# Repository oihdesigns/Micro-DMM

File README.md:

# Update Late August '25: 
I've recently started a new job. It's great, but has longer hours than my previous job. This will negatively affect the amount of time I put into this project...

# Micro-DMM

This is the PCB design and code for a 4.5 digit DMM/ instrumentation module. It is designed and written primairly for Arduino-style development boards.

I've developed this DMM in my work testing and troubleshooting electronics to make my life easier. 

I've had Deep-Wiki index my documentation. It did a mostly okay job. You can read its summary here:

## The main features are:

- The most recent designs have **open-lead detection in voltmeter mode**. I believe this makes it the first voltmeter in exisitance that can automatically, safely, and positively tell the difference between "there is low impedance between these points" vs "current does not and can not flow between these two points." Please see the white paper for details. 
- Using keyboard emulation to directly type values into a computer for me. (Extremely useful when troubleshooting a populated PCB - you can quickly ohm out both the problem board and a good one directly into Excel to look for different impedances between given contacts.)
- Very sensitive low-resistance readings (accurate to better than 0.01 Ohms with proper lead zeroing).
- LED blinks when I'm reading logic level voltage or higher.
- Simultaneous current and voltage measurement abilities (requires a Hall sensor-based ammeter module). 
- Data logging for current and voltage, with customizable triggers to autolog both.

## Raspberry Pi user interface

The repository now includes a Raspberry Pi-friendly interface that mirrors the firmware display and logging features. The UI is written in Python using Tkinter so it ships with Raspberry Pi OS and can run directly on the framebuffer or under X11. To start the dashboard with the built-in demo generator run:

```
python3 -m raspi_port.app
```

In deployment the measurement host should feed real readings to the `MicroDmmApp` class instead of the demo thread. The window presents the same information rendered by `updateDisplay()`—live voltage or resistance with min/max tracking, current when enabled, the active mode, timestamps, delta/null information, and log counters. Interaction hotkeys replace the touch panel:

| Function | Touch color | Hotkey | Description |
| --- | --- | --- | --- |
| Mode cycle | Red | `M` | Advances through the measurement modes. |
| Manual log | Green | `L` | Appends the most recent sample buffer to `~/micro_dmm_logs/data.csv`. |
| Auto log export | – | `A` | Writes the auto-log buffer to `~/micro_dmm_logs/data_autologged.csv`. |
| Min/Max reset | Blue | `Z` | Clears the stored extrema, just like tapping “Min/Max”. |
| Type/Δ | Yellow | `T` | In *Type* mode it writes the displayed value to `typed_entries.txt`; otherwise it arms the delta/null workflow. |

On a Raspberry Pi you can optionally map these controls to hardware buttons by defining a `MICRO_DMM_GPIO` environment variable before launching the program. The value is a comma-separated list such as `mode=5,manual_log=6,auto_log=13,minmax=19,type=26`. Each entry binds a GPIO pin (using `gpiozero.Button`) to the corresponding action.

All log exports stay on the Pi’s filesystem under `~/micro_dmm_logs/`. The CSV layouts match the firmware’s `logCurrentData()` and `autologArraysToCSV()` routines so downstream tooling continues to work. The `typed_entries.txt` file replaces the USB keyboard emulator and captures the same formatted text that would have been “typed” into a host PC, while also echoing it to stdout for quick clipboard-style use.

I have a long and detailed write-up of the circuitry design on my personal website: https://www.oihdesigns.com/arduino-multimeter-project

There are a couple videos here:
https://youtu.be/rzj-ar2Qv_A
and here:
https://youtu.be/hZ4eH-7RNsU

Here are more photos:

## Design Prioities and Compromises:
This meter is designed to complement and support the more expensive equimpent generally found in a lab, rather than replace it. With that in mide, I've made the following design decisions on my priorites:

### Minimal Protections
- The voltmeter circuitry is not designed to measure amplitudes higher than is dangerous to humans. By not designing a tool that is supposed to keep people safe I can dramatically simplify and shrink the design. (The said, I've nailed the voltmeter circuit with a 1000V megaohmmeter. No problem.)
- Likewise, the resistance circuit can be damaged if you accidentally measure too much /unregulated voltage. This is a tradeoff for a very fast and accurate autoranging ohmmeter circuit that can accurately read from less than 0.01 to more than 5,000,000 Ohms. 

### Streamlined Functions
- There is no built in ammeter, inductance, or capacitance function. Ammeter function is easily added as needed with either an off-the-shelf module, or a low value resistor across the voltmeter. There isn't an easy way to add indutance or capacitance. I don't use any of these often enough for them to be worth taking up the PCB space.  

## Current Support:
As of writing I have functional versions (I confirmed the core functions work) that support the:
- Arduino Uno R4
- Arduino Giga (with or without the display shield)
- Arduino ESP32 Nano (via jumpers)
- Seeed Studio XIAO RA4M1 (same processer as the Uno R4)
- I have partial function on a direct computer (Windows 11) interface with a FT232H breakout board (AdaFruit makes a nice one). I can see the data lines and it looks like most of the logic works, more or less. It's a proof of concept port and a test for "can I tell the AI to take an Arduino sketch and port it to Python" (the answer is far more yes than it use to be).
  -  That said, it's very slow (reading in at 2-3sps). I'm not sure how to optimize this, and speeding it up is not an immediate priority. 

# Future Plans:

## Major Function Things to Address:
- Writing to MicroSD cards over the AUX SPI Bux on the RA4M1 XIAO boards. I set this up and tested it, but it didn't work and needs to be troubleshot.
- Getting the code to run on the XIAO RP2350 board. It compiles but does not run. 

## Potential Refinements To-Do List:
- Revise the PCB design to shrink the physical size (the current design was made with hand-soldering in mind). This would involve:
  - Smaller footprint components for things like the pullup resistors.
  - Dedicated multiple transistor packages for the switching functions rather than the discreet components.
  - There are probably other ways to shrink the design.
  - There is some potential performance improvement room to the analog circuit if I take advantage of the ADS1115's max input voltage of ~6.144vdc instead of 5vdc.
- There is always room for cleanup in the code to make it more elegant. 

## Ideas for Expanding on the Current Function / :
- Make a version that uses an ADS1256 instead of the ADS1115 to support measurements speeds up to 30,000 samples/second and resolutions of up to 24bits. (I have had proof-of-concept success with this using a Raspberry PI ADS1256 hat.)
- Make a version that runs off a Raspberry Pi.
- Implement WiFi/Bluetooth features on the boards that support it.
- Implement DAC output as a simple function generator for the boards that support it.
- Add a jumper on the PCB and write the code to allow four-wire resistance readings.

If you're interested in helping develop this please feel free to reach out. 

# FAQ:
- Q: What is the logic voltage?
  - A:  The current PCB works for either 3.3 or 5vdc. 

- Q: Is there voltage isolation on the USB?
  - A: There is enough isolation (500K Ohms) that you will not hurt anything by measuring voltage (in either polarity) on something connected to the wall while the meter is also connected to the wall, but not enough to prevent ground loops from interfering with measurements. See the longer, full write up on my website, and then buy the Adafruit USB voltage isolation board.

- Q: The Adafruit isolation board says "100mA." What does the meter draw?
  - A: With the XIAO RA4M1, 50-60mA typical when measuring voltage. Closer to 100mA when measuring resistance. The resistance circuit goes into low-power mode several seconds after being open (except in a no-sleep mode).

- Q: Does it work on an Arduino Uno R3?
  - A: As a basic meter, yes, but there's no keyboard emulation.    

- Q: Can I buy one?
  - A: Eventually, yes, probably? I do not have a current timeline for bringing these to market. If you want one please reach out to me. If you want to hand-solder it yourself I can sell you a single PCB and maybe some of the components with higher individual costs.

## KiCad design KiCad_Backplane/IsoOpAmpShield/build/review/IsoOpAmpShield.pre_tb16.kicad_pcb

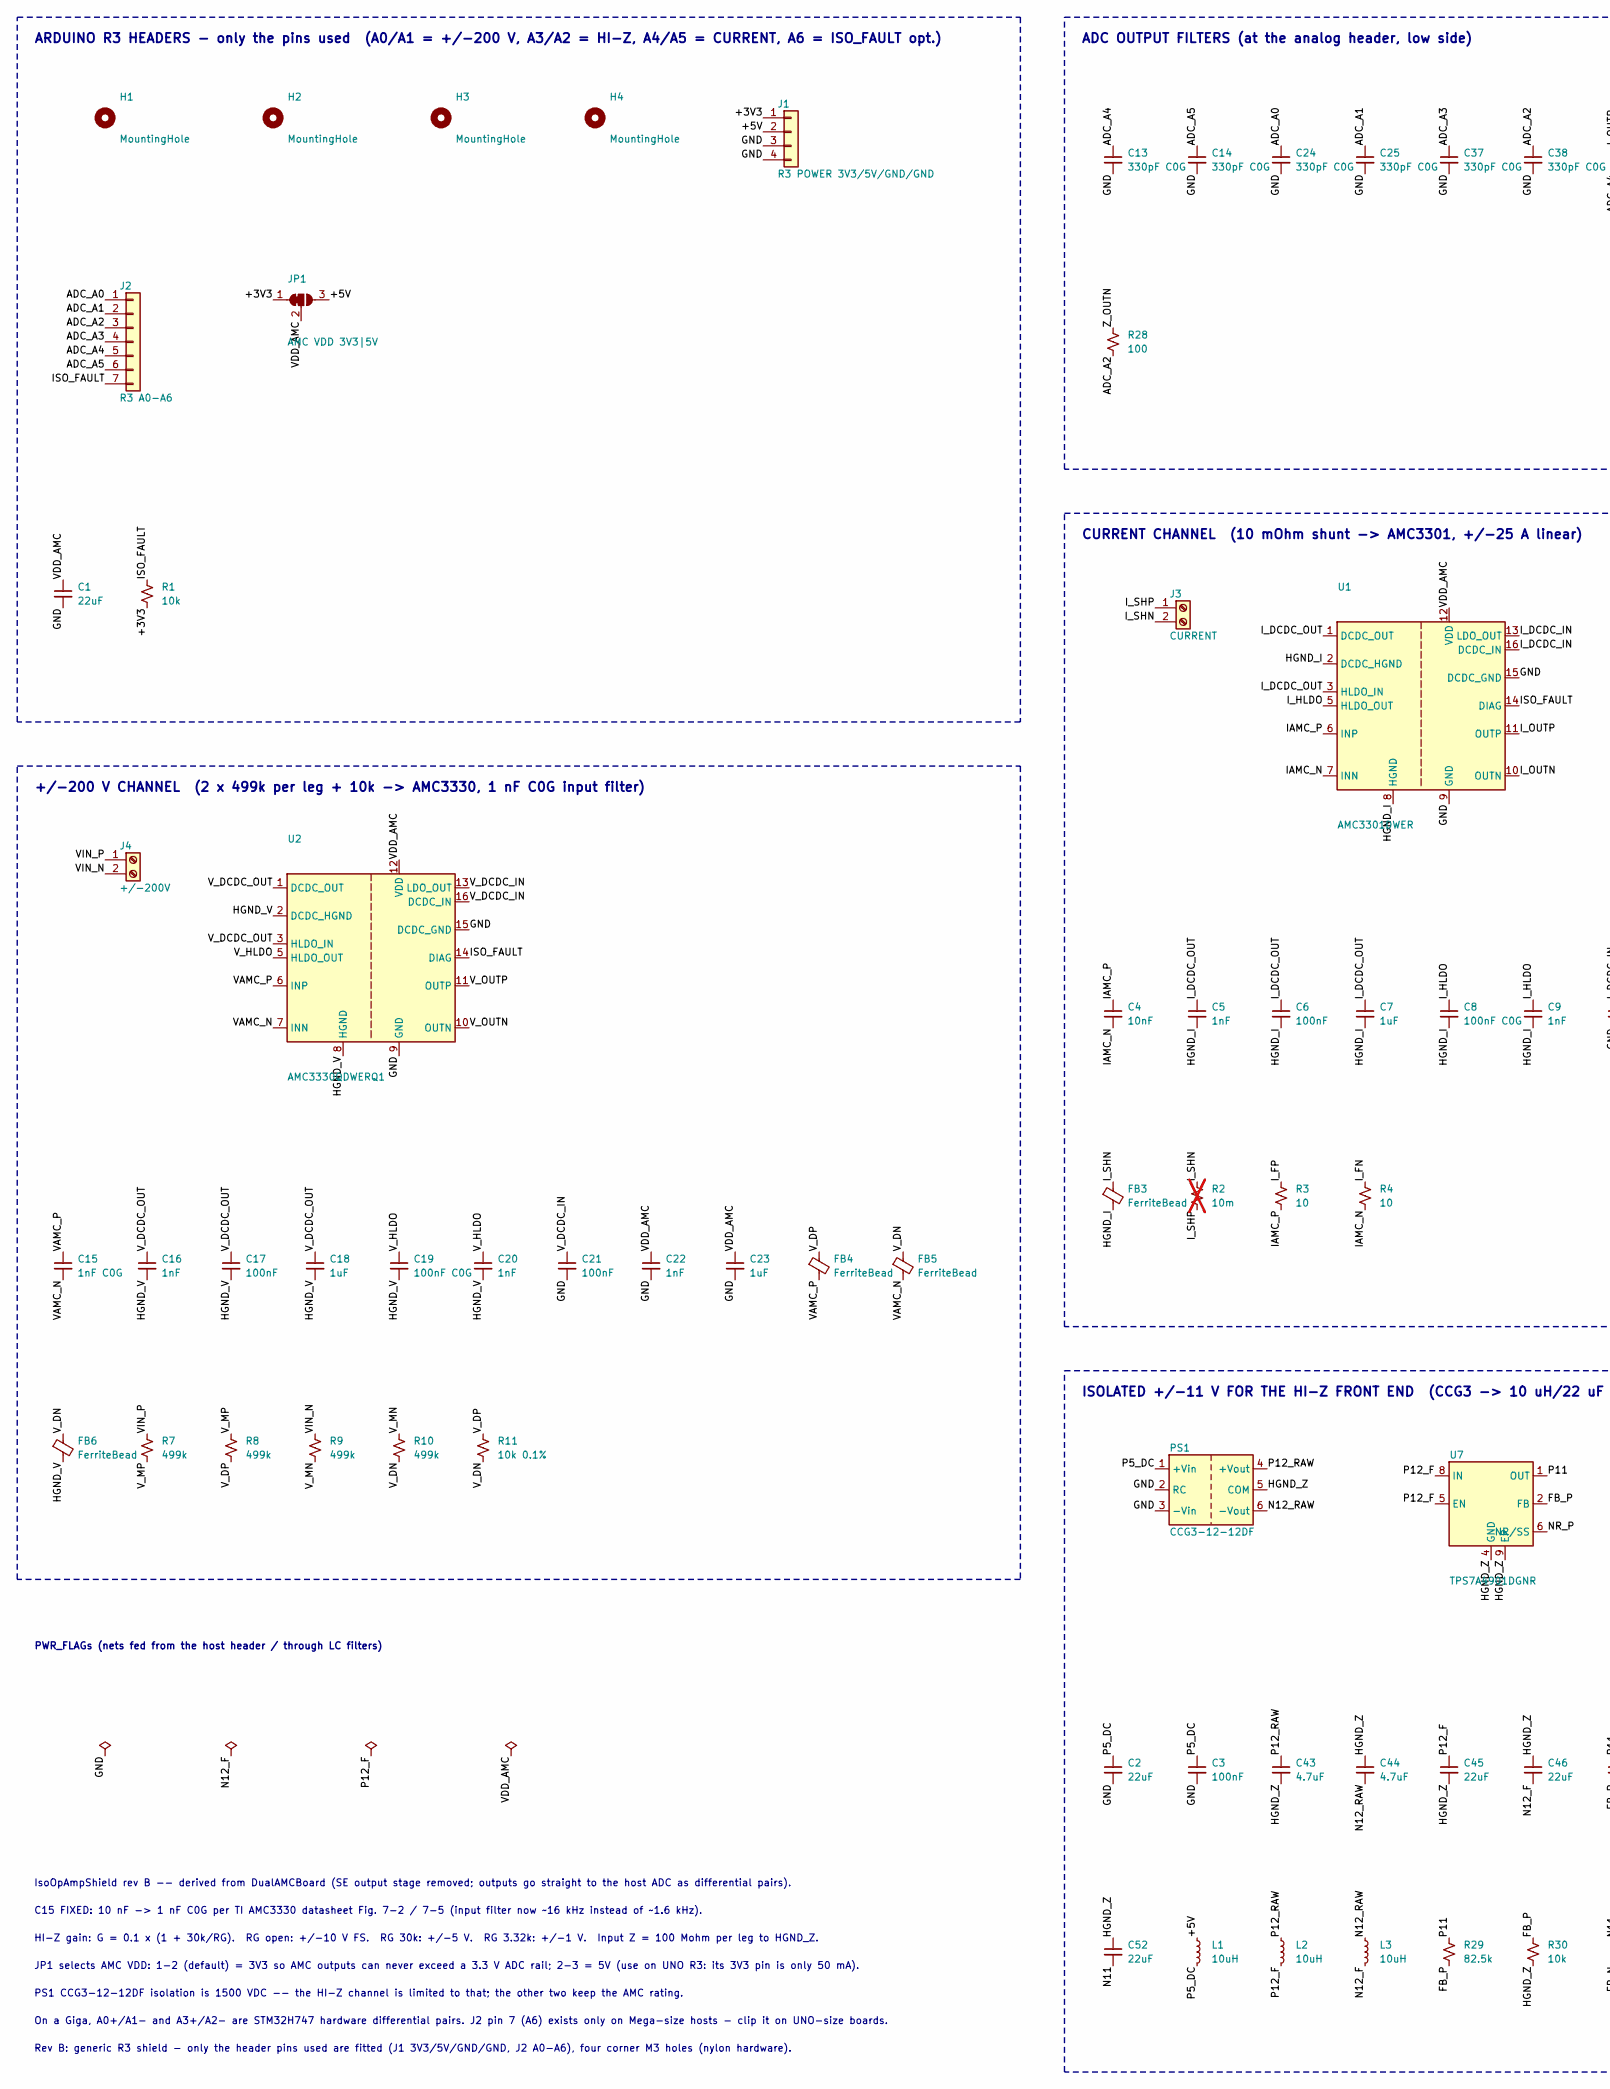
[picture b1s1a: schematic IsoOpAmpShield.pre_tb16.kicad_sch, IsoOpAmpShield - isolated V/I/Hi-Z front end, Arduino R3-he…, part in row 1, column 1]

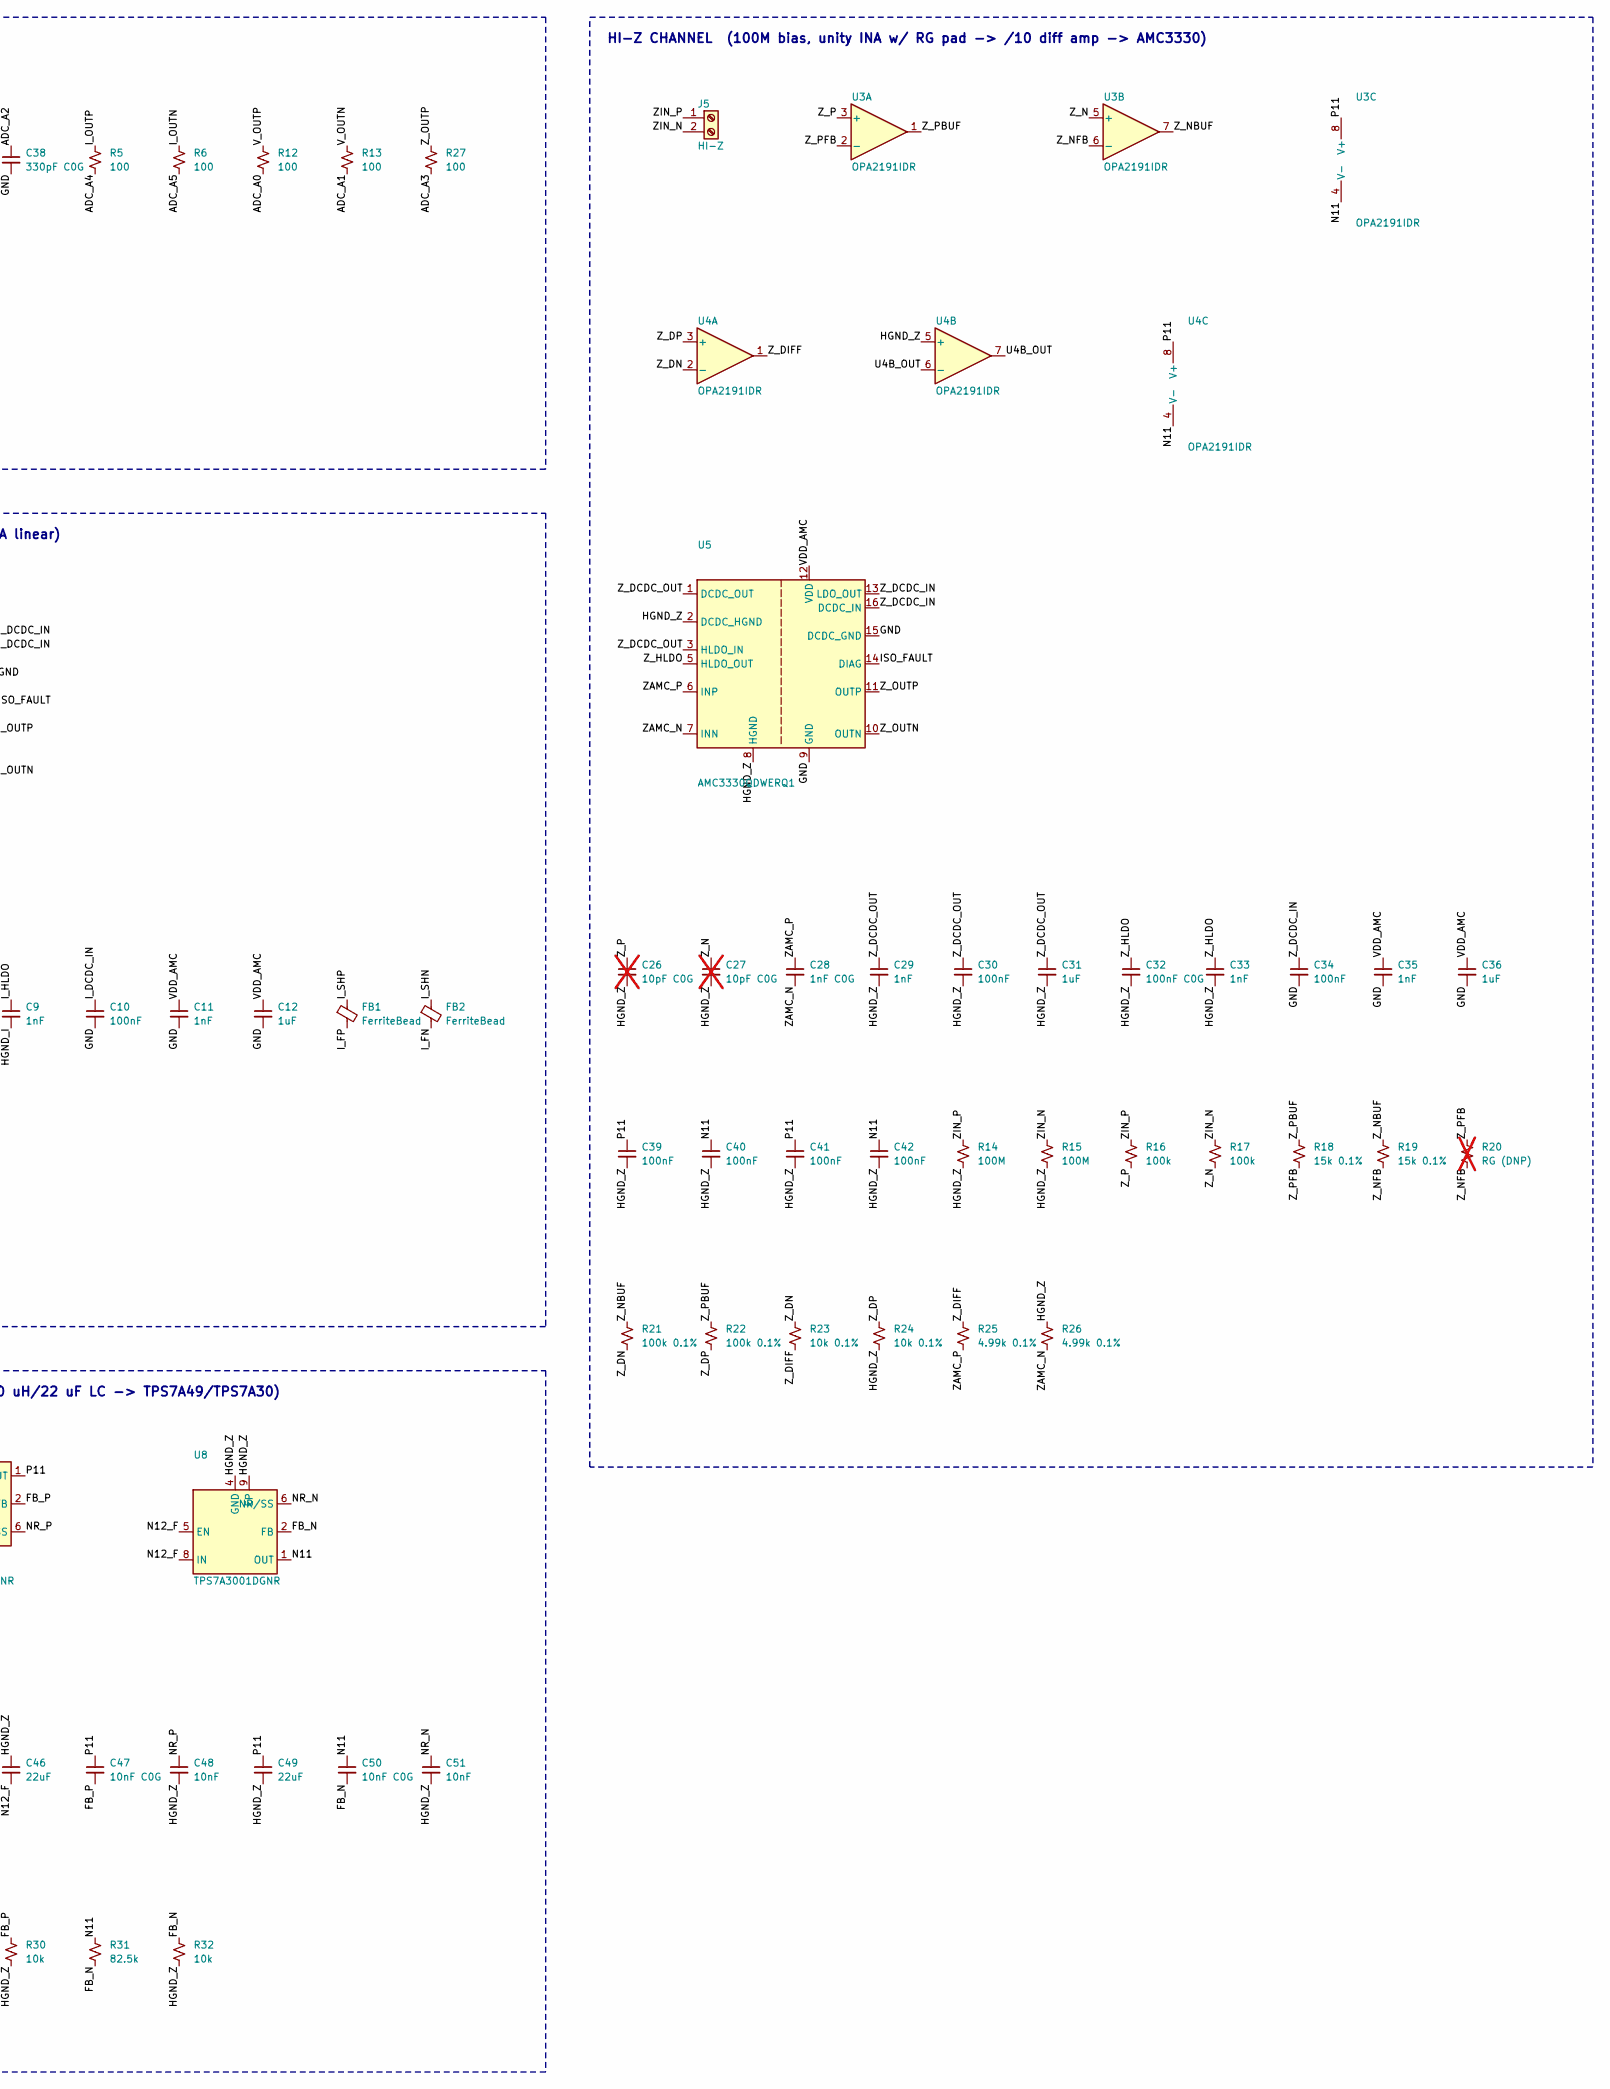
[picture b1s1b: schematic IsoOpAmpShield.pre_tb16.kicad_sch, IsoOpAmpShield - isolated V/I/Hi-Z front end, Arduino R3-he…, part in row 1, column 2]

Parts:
C1, C2, C45, C46, C49, C52: 22uF; C_0805_2012Metric_Pad1.18x1.45mm_HandSolder
C3, C6, C10, C17, C21, C30, C34, C39, C40, C41, C42: 100nF; C_0603_1608Metric_Pad1.08x0.95mm_HandSolder
C4: 10nF; C_0805_2012Metric_Pad1.18x1.45mm_HandSolder
C5, C16, C29: 1nF; C_0603_1608Metric_Pad1.08x0.95mm_HandSolder
C7, C18, C31: 1uF; C_0603_1608Metric_Pad1.08x0.95mm_HandSolder
C8, C19, C32: 100nF C0G; C_1206_3216Metric_Pad1.33x1.80mm_HandSolder
C9, C11, C20, C22, C33, C35: 1nF; C_1206_3216Metric_Pad1.33x1.80mm_HandSolder
C12, C23, C36: 1uF; C_1206_3216Metric_Pad1.33x1.80mm_HandSolder
C13, C14, C24, C25, C37, C38: 330pF C0G; C_0603_1608Metric_Pad1.08x0.95mm_HandSolder
C15, C28: 1nF C0G; C_0805_2012Metric_Pad1.18x1.45mm_HandSolder
C26, C27: 10pF C0G; C_0603_1608Metric_Pad1.08x0.95mm_HandSolder; not fitted
C43, C44: 4.7uF; C_0805_2012Metric_Pad1.18x1.45mm_HandSolder
C47, C50: 10nF C0G; C_0603_1608Metric_Pad1.08x0.95mm_HandSolder
C48, C51: 10nF; C_0603_1608Metric_Pad1.08x0.95mm_HandSolder
FB1, FB2, FB3, FB4, FB5, FB6: FerriteBead; L_0402_1005Metric_Pad0.77x0.64mm_HandSolder
H1, H2, H3, H4: MountingHole; MountingHole_3.2mm_M3_NPTH
J1: R3 POWER 3V3/5V/GND/GND; PinHeader_1x04_P2.54mm_Vertical
J2: R3 A0-A6; PinHeader_1x07_P2.54mm_Vertical
J3: CURRENT; TerminalBlock_RND_205-00232_1x02_P5.08mm_Horizontal
J4: +/-200V; TerminalBlock_RND_205-00232_1x02_P5.08mm_Horizontal
J5: HI-Z; TerminalBlock_RND_205-00232_1x02_P5.08mm_Horizontal
JP1: AMC VDD 3V3|5V; SolderJumper-3_P1.3mm_Bridged12_RoundedPad1.0x1.5mm
L1, L2, L3: 10uH; L_1210_3225Metric_Pad1.42x2.65mm_HandSolder
PS1: CCG3-12-12DF; TDK_CCG3_Dual_THT
R1, R30, R32: 10k; R_0805_2012Metric_Pad1.20x1.40mm_HandSolder
R2: 10m; R_2010_5025Metric_Pad1.40x2.65mm_HandSolder; not fitted
R3, R4: 10; R_0805_2012Metric_Pad1.20x1.40mm_HandSolder
R5, R6, R12, R13, R27, R28: 100; R_0805_2012Metric_Pad1.20x1.40mm_HandSolder
R7, R8, R9, R10: 499k; R_0805_2012Metric_Pad1.20x1.40mm_HandSolder
R11, R23, R24: 10k 0.1%; R_0805_2012Metric_Pad1.20x1.40mm_HandSolder
R14, R15: 100M; R_1206_3216Metric_Pad1.30x1.75mm_HandSolder
R16, R17: 100k; R_1206_3216Metric_Pad1.30x1.75mm_HandSolder
R18, R19: 15k 0.1%; R_0805_2012Metric_Pad1.20x1.40mm_HandSolder
R20: RG (DNP); R_0805_2012Metric_Pad1.20x1.40mm_HandSolder; not fitted
R21, R22: 100k 0.1%; R_0805_2012Metric_Pad1.20x1.40mm_HandSolder
R25, R26: 4.99k 0.1%; R_0805_2012Metric_Pad1.20x1.40mm_HandSolder
R29, R31: 82.5k; R_0805_2012Metric_Pad1.20x1.40mm_HandSolder
U1: AMC3301DWER; SOIC-16W_7.5x10.3mm_P1.27mm
U2, U5: AMC3330QDWERQ1; SOIC-16W_7.5x10.3mm_P1.27mm
U3, U4: OPA2191IDR; SOIC-8_3.9x4.9mm_P1.27mm
U7: TPS7A4901DGNR; HVSSOP-8-1EP_3x3mm_P0.65mm_EP1.57x1.89mm
U8: TPS7A3001DGNR; HVSSOP-8-1EP_3x3mm_P0.65mm_EP1.57x1.89mm

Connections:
/+3V3: J1.1, JP1.1 (A), R1.2
/+5V: J1.2, JP1.3 (B), L1.1
/ADC_A0: C24.1, J2.1, R12.2
/ADC_A1: C25.1, J2.2, R13.2
/ADC_A2: C38.1, J2.3, R28.2
/ADC_A3: C37.1, J2.4, R27.2
/ADC_A4: C13.1, J2.5, R5.2
/ADC_A5: C14.1, J2.6, R6.2
/FB_N: C50.2, R31.2, R32.1, U8.2 (FB)
/FB_P: C47.2, R29.2, R30.1, U7.2 (FB)
/GND: C1.2, C2.2, C3.2, C10.2, C11.2, C12.2, C13.2, C14.2, C21.2, C22.2, C23.2, C24.2, C25.2, C34.2, C35.2, C36.2, C37.2, C38.2, J1.3, J1.4, PS1.2 (RC), PS1.3 (-Vin), U1.9 (GND), U1.15 (DCDC_GND), U2.9 (GND), U2.15 (DCDC_GND), U5.9 (GND), U5.15 (DCDC_GND)
/HGND_I: C5.2, C6.2, C7.2, C8.2, C9.2, FB3.2, U1.2 (DCDC_HGND), U1.8 (HGND)
/HGND_V: C16.2, C17.2, C18.2, C19.2, C20.2, FB6.2, U2.2 (DCDC_HGND), U2.8 (HGND)
/HGND_Z: C26.2, C27.2, C29.2, C30.2, C31.2, C32.2, C33.2, C39.2, C40.2, C41.2, C42.2, C43.2, C44.1, C45.2, C46.1, C48.2, C49.2, C51.2, C52.1, PS1.5 (COM), R14.2, R15.2, R24.2, R26.1, R30.2, R32.2, U4.5 (+), U5.2 (DCDC_HGND), U5.8 (HGND), U7.4 (GND), U7.9 (EP), U8.4 (GND), U8.9 (EP)
/IAMC_N: C4.2, R4.2, U1.7 (INN)
/IAMC_P: C4.1, R3.2, U1.6 (INP)
/ISO_FAULT: J2.7, R1.1, U1.14 (DIAG), U2.14 (DIAG), U5.14 (DIAG)
/I_DCDC_IN: C10.1, U1.13 (LDO_OUT), U1.16 (DCDC_IN)
/I_DCDC_OUT: C5.1, C6.1, C7.1, U1.1 (DCDC_OUT), U1.3 (HLDO_IN)
/I_FN: FB2.2, R4.1
/I_FP: FB1.2, R3.1
/I_HLDO: C8.1, C9.1, U1.5 (HLDO_OUT)
/I_OUTN: R6.1, U1.10 (OUTN)
/I_OUTP: R5.1, U1.11 (OUTP)
/I_SHN: FB2.1, FB3.1, J3.2, R2.1
/I_SHP: FB1.1, J3.1, R2.2
/N11: C40.1, C42.1, C50.1, C52.2, R31.1, U3.4 (V-), U4.4 (V-), U8.1 (OUT)
/N12_F: C46.2, L3.2, U8.5 (EN), U8.8 (IN)
/N12_RAW: C44.2, L3.1, PS1.6 (-Vout)
/NR_N: C51.1, U8.6 (NR/SS)
/NR_P: C48.1, U7.6 (NR/SS)
/P5_DC: C2.1, C3.1, L1.2, PS1.1 (+Vin)
/P11: C39.1, C41.1, C47.1, C49.1, R29.1, U3.8 (V+), U4.8 (V+), U7.1 (OUT)
/P12_F: C45.1, L2.2, U7.5 (EN), U7.8 (IN)
/P12_RAW: C43.1, L2.1, PS1.4 (+Vout)
/U4B_OUT: U4.6 (-), U4.7
/VAMC_N: C15.2, FB5.2, U2.7 (INN)
/VAMC_P: C15.1, FB4.2, U2.6 (INP)
/VDD_AMC: C1.1, C11.1, C12.1, C22.1, C23.1, C35.1, C36.1, JP1.2 (C), U1.12 (VDD), U2.12 (VDD), U5.12 (VDD)
/VIN_N: J4.2, R9.1
/VIN_P: J4.1, R7.1
/V_DCDC_IN: C21.1, U2.13 (LDO_OUT), U2.16 (DCDC_IN)
/V_DCDC_OUT: C16.1, C17.1, C18.1, U2.1 (DCDC_OUT), U2.3 (HLDO_IN)
/V_DN: FB5.1, FB6.1, R10.2, R11.2
/V_DP: FB4.1, R8.2, R11.1
/V_HLDO: C19.1, C20.1, U2.5 (HLDO_OUT)
/V_MN: R9.2, R10.1
/V_MP: R7.2, R8.1
/V_OUTN: R13.1, U2.10 (OUTN)
/V_OUTP: R12.1, U2.11 (OUTP)
/ZAMC_N: C28.2, R26.2, U5.7 (INN)
/ZAMC_P: C28.1, R25.2, U5.6 (INP)
/ZIN_N: J5.2, R15.1, R17.1
/ZIN_P: J5.1, R14.1, R16.1
/Z_DCDC_IN: C34.1, U5.13 (LDO_OUT), U5.16 (DCDC_IN)
/Z_DCDC_OUT: C29.1, C30.1, C31.1, U5.1 (DCDC_OUT), U5.3 (HLDO_IN)
/Z_DIFF: R23.2, R25.1, U4.1
/Z_DN: R21.2, R23.1, U4.2 (-)
/Z_DP: R22.2, R24.1, U4.3 (+)
/Z_HLDO: C32.1, C33.1, U5.5 (HLDO_OUT)
/Z_N: C27.1, R17.2, U3.5 (+)
/Z_NBUF: R19.1, R21.1, U3.7
/Z_NFB: R19.2, R20.2, U3.6 (-)
/Z_OUTN: R28.1, U5.10 (OUTN)
/Z_OUTP: R27.1, U5.11 (OUTP)
/Z_P: C26.1, R16.2, U3.3 (+)
/Z_PBUF: R18.1, R22.1, U3.1
/Z_PFB: R18.2, R20.1, U3.2 (-)

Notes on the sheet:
ARDUINO R3 HEADERS - only the pins used (A0/A1 = +/-200 V, A3/A2 = HI-Z, A4/A5 = CURRENT, A6 = ISO_FAULT opt.)
+/-200 V CHANNEL (2 x 499k per leg + 10k -> AMC3330, 1 nF C0G input filter)
ADC OUTPUT FILTERS (at the analog header, low side)
CURRENT CHANNEL (10 mOhm shunt -> AMC3301, +/-25 A linear)
ISOLATED +/-11 V FOR THE HI-Z FRONT END (CCG3 -> 10 uH/22 uF LC -> TPS7A49/TPS7A30)
HI-Z CHANNEL (100M bias, unity INA w/ RG pad -> /10 diff amp -> AMC3330)
PWR_FLAGs (nets fed from the host header / through LC filters)
IsoOpAmpShield rev B -- derived from DualAMCBoard (SE output stage removed; outputs go straight to the host ADC as differential pairs).
C15 FIXED: 10 nF -> 1 nF C0G per TI AMC3330 datasheet Fig. 7-2 / 7-5 (input filter now ~16 kHz instead of ~1.6 kHz).
HI-Z gain: G = 0.1 x (1 + 30k/RG). RG open: +/-10 V FS. RG 30k: +/-5 V. RG 3.32k: +/-1 V. Input Z = 100 Mohm per leg to HGND_Z.
JP1 selects AMC VDD: 1-2 (default) = 3V3 so AMC outputs can never exceed a 3.3 V ADC rail; 2-3 = 5V (use on UNO R3: its 3V3 pin is only 50 mA).
PS1 CCG3-12-12DF isolation is 1500 VDC -- the HI-Z channel is limited to that; the other two keep the AMC rating.
On a Giga, A0+/A1- and A3+/A2- are STM32H747 hardware differential pairs. J2 pin 7 (A6) exists only on Mega-size hosts - clip it on UNO-size boards.
Rev B: generic R3 shield - only the header pins used are fitted (J1 3V3/5V/GND/GND, J2 A0-A6), four corner M3 holes (nylon hardware).

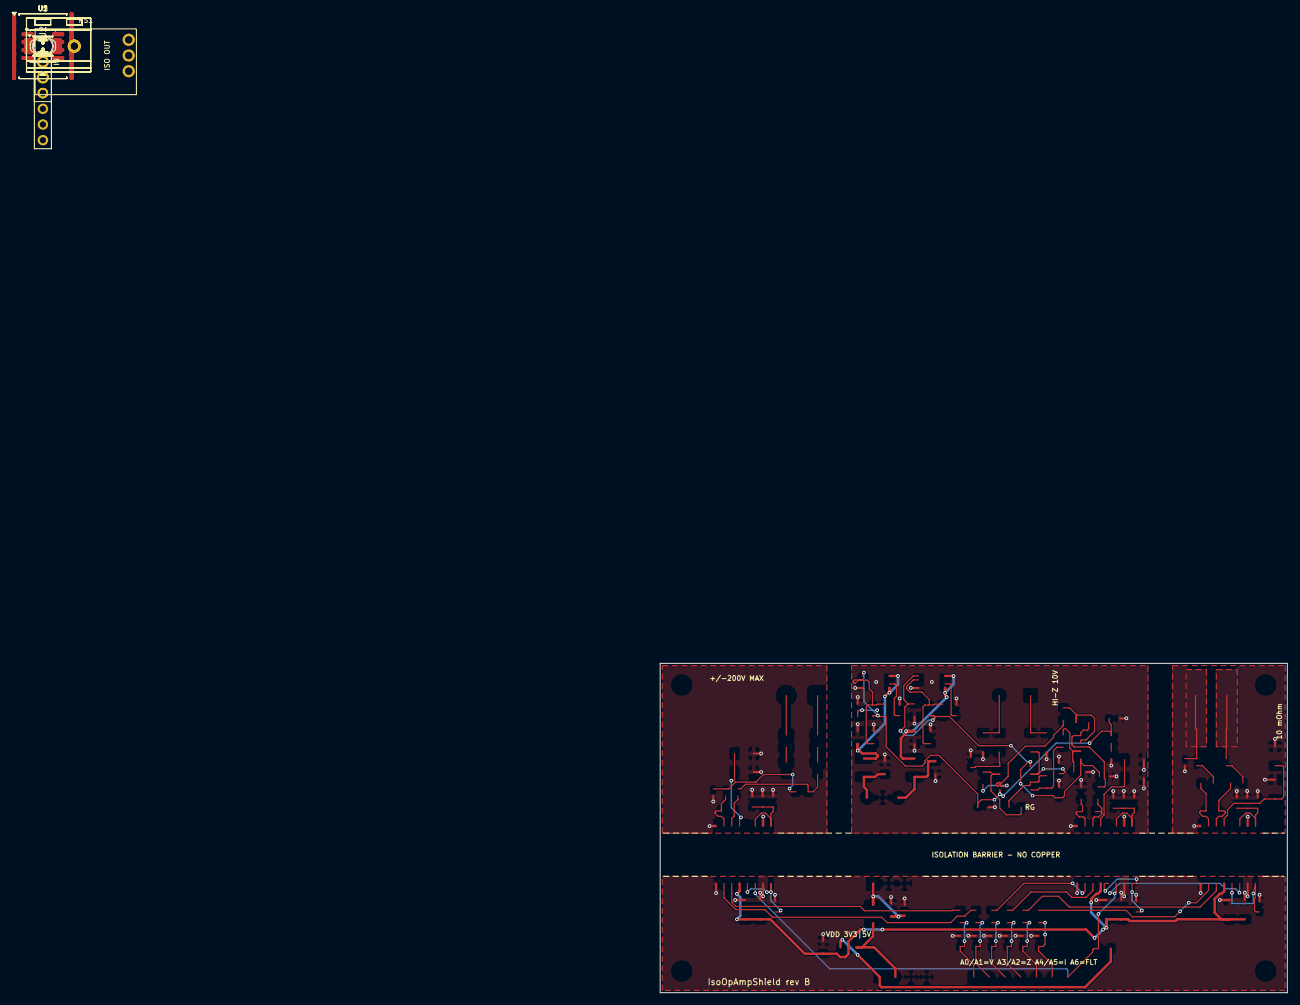
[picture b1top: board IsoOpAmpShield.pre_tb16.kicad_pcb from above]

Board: 4 copper layers, 101.6 x 53.3 mm, 111 parts (0 on the bottom side), 68 nets.

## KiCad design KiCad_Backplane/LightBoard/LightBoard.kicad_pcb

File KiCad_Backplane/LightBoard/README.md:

# LightBoard rev A

A 4-channel bright white LED board, 56 x 36 mm, 4 layers, built almost entirely from parts in
`AvaliableParts/Combined_parts_DigiKey_and_Mouser.xlsx`.

- **LEDs:** 4 x Samsung LH351D 4000 K (SPHWHTL3DA0GF4TPQ6) in a 2 x 2 cluster with 8 mm pitch.
- **Drivers:** 4 x MIC4801YM, a 600 mA linear current sink, one per LED.
- **Supply:** +5 V on J1 (**5.5 V max**; the MIC4801 is a 6 V part). A low-side N-FET
  (Q1, AOSS32334C) gives reverse-polarity protection.
- **Control:** SW1 **ON** runs all four LEDs at full set current. SW1 **EXT** takes enable/PWM
  from J2 (3.3 V or 5 V logic, 200 Hz to 10 kHz for linear dimming). With nothing connected
  to J2, the LEDs stay off. The first PWM pulse after more than 40 ms low must be at least
  60 µs long to wake the MIC4801.

## Current setting (R5-R8, one per channel)

ILED = 4920 / (RSET[kΩ] - 0.14)

| RSET | Current per LED | Board input | Notes |
|---|---|---|---|
| 22k | 225 mA | 0.9 A | |
| **15k (default)** | **331 mA** | **1.35 A** | about 6.5 W of heat in total |
| 10k | 499 mA | 2.0 A | about 10 W of heat; needs a real heatsink |

## Why the 2.7 Ω resistors (R1-R4) are there

They are the only parts that are **not in stock**: Yageo RC2512FK-7W2R7L, 2512, 2 W (LCSC C5843102).

With a 5 V supply, each LED leaves about 2.2 V of headroom. Without a dropper, the SOIC-8 would
have to burn all of it (about 0.75 W per chip at 331 mA, with θJA ≈ 99 °C/W). The resistor takes
0.9 V of that, which leaves the MIC4801 about 0.45 W. If you run the board from a 1-cell Li-ion
(3.0-4.2 V), fit 0 Ω links instead.

## Heat: read this before powering up

This is a linear driver, so all the power drawn from the 5 V input ends up as heat on this small
board: about 6.5 W at the default current.

- **Bolt it to a heatsink.** Use an aluminium plate of roughly 100 cm² or more, with a thermal pad
  between it and the board, and the four M3 holes.
- The back copper (B.Cu) is GND and sits under solder mask.
- Each LED's thermal pad (electrically isolated) is tied to GND copper, with via arrays above,
  between and below the LED rows.
- Bare on the bench, use EXT with a low PWM duty cycle.

## Assembly notes

- The LH351D thermal pad sits under the part, so it needs a hot plate or hot air, not an iron.
- Check SW1's ON/EXT direction with a meter. The silk assumes that the actuator on the pin-1
  side connects common (pin 2) to pin 1.

## Files

- `tools/design.py` is the single source of truth for the circuit.
- `tools/make_lib.py` builds the symbols and the LH351D footprint. The footprint follows the
  datasheet Rev 9.1, p.16 recommended pattern.
- `tools/gen_sch.py` and `tools/gen_pcb.py` regenerate the schematic and the **fully routed**
  board. The PCB generator does the routing itself: explicit tracks plus an automatic plane-via
  placer.
- After running `gen_pcb.py`, refill the zones with
  `kicad-cli pcb drc --refill-zones --save-board LightBoard.kicad_pcb`.

Status (2026-11-22): ERC 0. DRC 0 errors, 0 unconnected, schematic parity 0; 4 silk-at-edge
warnings remain from the flush terminal blocks. Not fabricated.

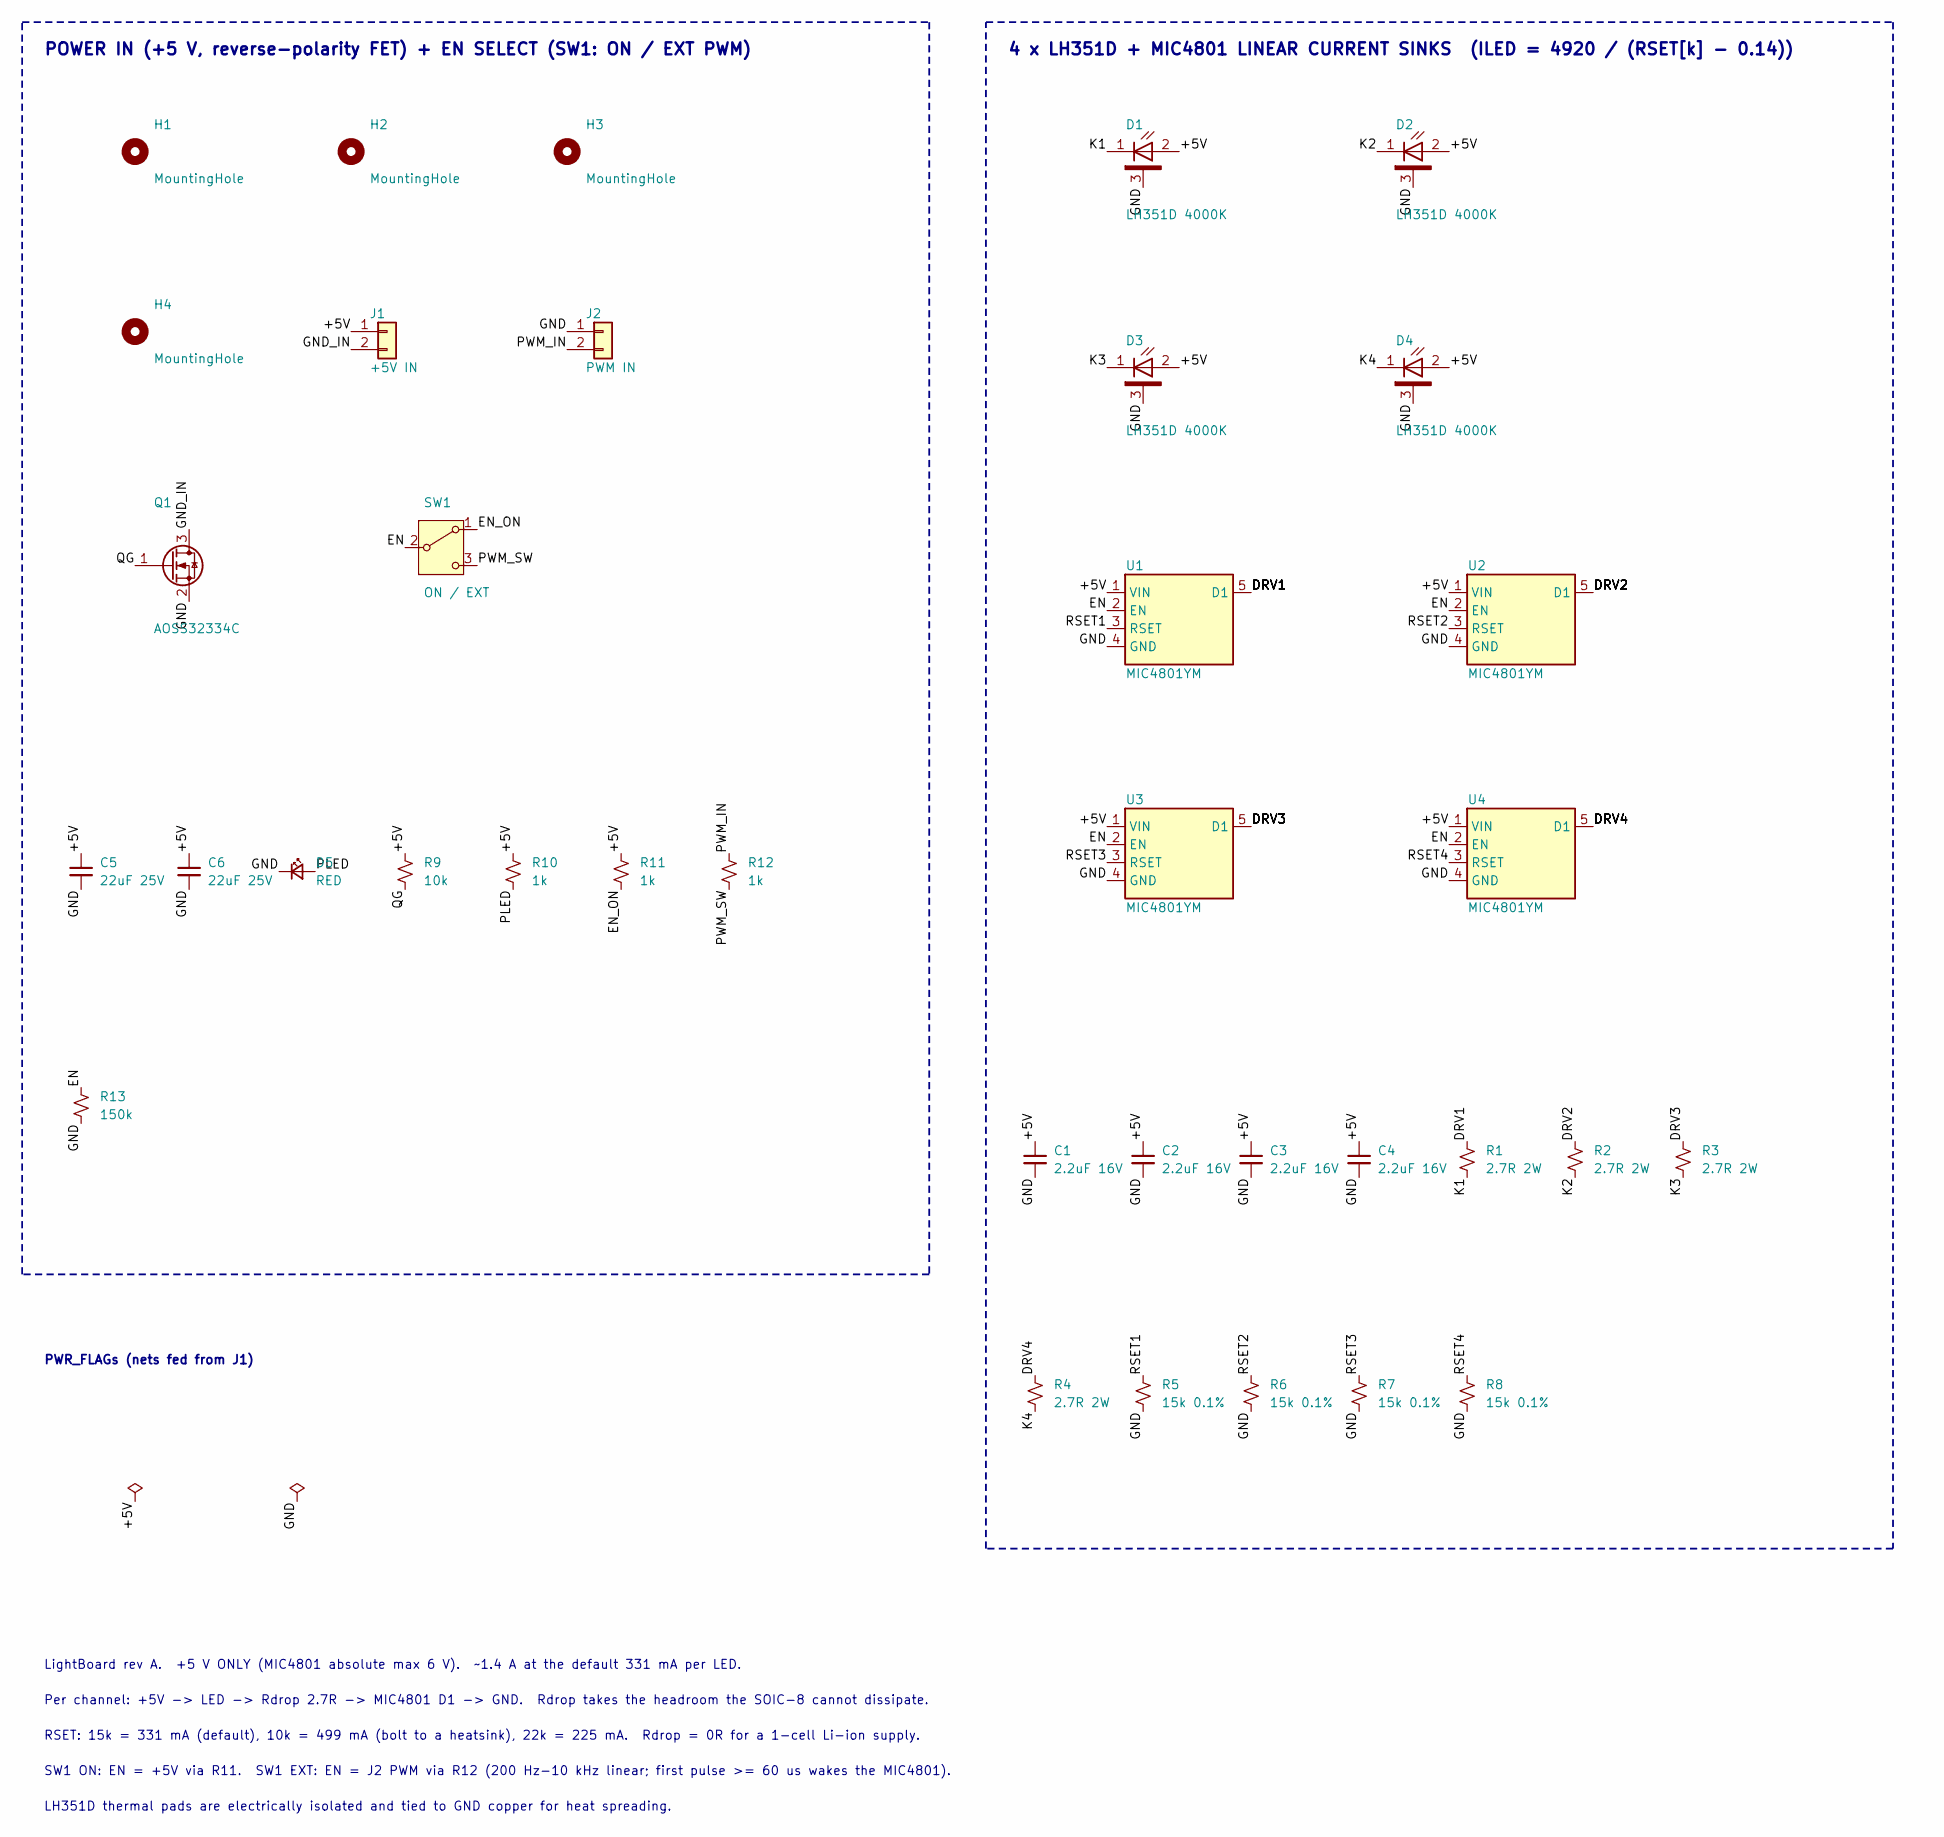
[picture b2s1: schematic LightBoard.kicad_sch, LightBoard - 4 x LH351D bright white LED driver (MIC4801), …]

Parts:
C1, C2, C3, C4: 2.2uF 16V; C_0805_2012Metric_Pad1.18x1.45mm_HandSolder
C5, C6: 22uF 25V; C_0805_2012Metric_Pad1.18x1.45mm_HandSolder
D1, D2, D3, D4: LH351D 4000K; LED_Samsung_LH351D_3.5x3.5mm
D5: RED; LED_0805_2012Metric_Pad1.15x1.40mm_HandSolder
H1, H2, H3, H4: MountingHole; MountingHole_3.2mm_M3
J1: +5V IN; TerminalBlock_Phoenix_MPT-0,5-2-2.54_1x02_P2.54mm_Horizontal
J2: PWM IN; TerminalBlock_Phoenix_MPT-0,5-2-2.54_1x02_P2.54mm_Horizontal
Q1: AOSS32334C; SOT-23
R1, R2, R3, R4: 2.7R 2W; R_2512_6332Metric_Pad1.40x3.35mm_HandSolder
R5, R6, R7, R8: 15k 0.1%; R_0805_2012Metric_Pad1.20x1.40mm_HandSolder
R9: 10k; R_0805_2012Metric_Pad1.20x1.40mm_HandSolder
R10, R11, R12: 1k; R_0805_2012Metric_Pad1.20x1.40mm_HandSolder
R13: 150k; R_0805_2012Metric_Pad1.20x1.40mm_HandSolder
SW1: ON / EXT; SW_Slide_SPDT_Angled_CK_OS102011MA1Q
U1, U2, U3, U4: MIC4801YM; SOIC-8_3.9x4.9mm_P1.27mm

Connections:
/+5V: C1.1, C2.1, C3.1, C4.1, C5.1, C6.1, D1.2 (A), D2.2 (A), D3.2 (A), D4.2 (A), J1.1, R9.1, R10.1, R11.1, U1.1 (VIN), U2.1 (VIN), U3.1 (VIN), U4.1 (VIN)
/DRV1: R1.1, U1.5 (D1), U1.6 (D1), U1.7 (D1), U1.8 (D1)
/DRV2: R2.1, U2.5 (D1), U2.6 (D1), U2.7 (D1), U2.8 (D1)
/DRV3: R3.1, U3.5 (D1), U3.6 (D1), U3.7 (D1), U3.8 (D1)
/DRV4: R4.1, U4.5 (D1), U4.6 (D1), U4.7 (D1), U4.8 (D1)
/EN: R13.1, SW1.2 (B), U1.2 (EN), U2.2 (EN), U3.2 (EN), U4.2 (EN)
/EN_ON: R11.2, SW1.1 (A)
/GND: C1.2, C2.2, C3.2, C4.2, C5.2, C6.2, D1.3 (TP), D2.3 (TP), D3.3 (TP), D4.3 (TP), D5.1 (K), J2.1, Q1.2 (S), R5.2, R6.2, R7.2, R8.2, R13.2, U1.4 (GND), U2.4 (GND), U3.4 (GND), U4.4 (GND)
/GND_IN: J1.2, Q1.3 (D)
/K1: D1.1 (K), R1.2
/K2: D2.1 (K), R2.2
/K3: D3.1 (K), R3.2
/K4: D4.1 (K), R4.2
/PLED: D5.2 (A), R10.2
/PWM_IN: J2.2, R12.1
/PWM_SW: R12.2, SW1.3 (C)
/QG: Q1.1 (G), R9.2
/RSET1: R5.1, U1.3 (RSET)
/RSET2: R6.1, U2.3 (RSET)
/RSET3: R7.1, U3.3 (RSET)
/RSET4: R8.1, U4.3 (RSET)

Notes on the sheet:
POWER IN (+5 V, reverse-polarity FET) + EN SELECT (SW1: ON / EXT PWM)
4 x LH351D + MIC4801 LINEAR CURRENT SINKS (ILED = 4920 / (RSET[k] - 0.14))
PWR_FLAGs (nets fed from J1)
LightBoard rev A. +5 V ONLY (MIC4801 absolute max 6 V). ~1.4 A at the default 331 mA per LED.
Per channel: +5V -> LED -> Rdrop 2.7R -> MIC4801 D1 -> GND. Rdrop takes the headroom the SOIC-8 cannot dissipate.
RSET: 15k = 331 mA (default), 10k = 499 mA (bolt to a heatsink), 22k = 225 mA. Rdrop = 0R for a 1-cell Li-ion supply.
SW1 ON: EN = +5V via R11. SW1 EXT: EN = J2 PWM via R12 (200 Hz-10 kHz linear; first pulse >= 60 us wakes the MIC4801).
LH351D thermal pads are electrically isolated and tied to GND copper for heat spreading.

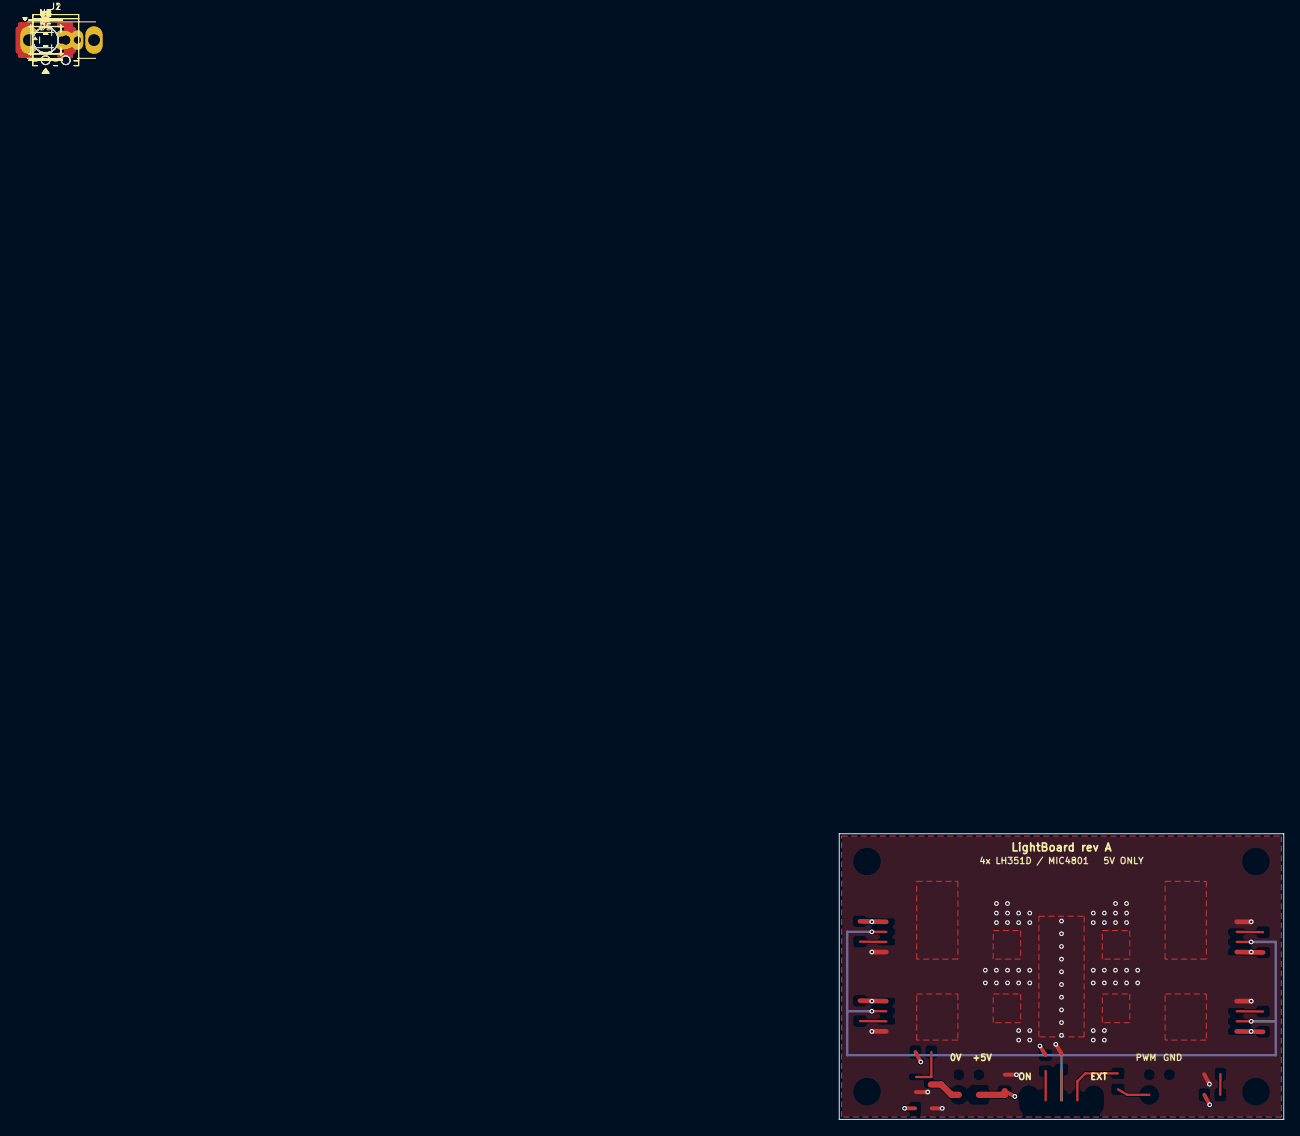
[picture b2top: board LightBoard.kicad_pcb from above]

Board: 4 copper layers, 56.0 x 36.0 mm, 36 parts (0 on the bottom side), 21 nets.

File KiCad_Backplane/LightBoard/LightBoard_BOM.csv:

Refs,Qty,Value,MPN,Footprint,In stock (AvaliableParts)
C1 C2 C3 C4,4,2.2uF 16V,CL21B225KOFNNNE,C_0805_2012Metric_Pad1.18x1.45mm_HandSolder,yes
C5 C6,2,22uF 25V,CL21A226MAYNNNE,C_0805_2012Metric_Pad1.18x1.45mm_HandSolder,yes
D1 D2 D3 D4,4,LH351D 4000K,SPHWHTL3DA0GF4TPQ6,LED_Samsung_LH351D_3.5x3.5mm,yes
D5,1,RED,LS R976-NR-1-0-20-R18,LED_0805_2012Metric_Pad1.15x1.40mm_HandSolder,yes
J1,1,+5V IN,1725656,"TerminalBlock_Phoenix_MPT-0,5-2-2.54_1x02_P2.54mm_Horizontal",yes
J2,1,PWM IN,1725656,"TerminalBlock_Phoenix_MPT-0,5-2-2.54_1x02_P2.54mm_Horizontal",yes
Q1,1,AOSS32334C,AOSS32334C,SOT-23,yes
R1 R2 R3 R4,4,2.7R 2W,RC2512FK-7W2R7L,R_2512_6332Metric_Pad1.40x3.35mm_HandSolder,NO - order
R5 R6 R7 R8,4,15k 0.1%,RG2012P-153-B-T5,R_0805_2012Metric_Pad1.20x1.40mm_HandSolder,yes
R9,1,10k,RN73H2ATTD1002B25,R_0805_2012Metric_Pad1.20x1.40mm_HandSolder,yes
R10 R11 R12,3,1k,RR1220P-102-D,R_0805_2012Metric_Pad1.20x1.40mm_HandSolder,yes
R13,1,150k,ERA-6AED154V,R_0805_2012Metric_Pad1.20x1.40mm_HandSolder,yes
SW1,1,ON / EXT,OS102011MA1QN1,SW_Slide_SPDT_Angled_CK_OS102011MA1Q,yes
U1 U2 U3 U4,4,MIC4801YM,MIC4801YM-TR,SOIC-8_3.9x4.9mm_P1.27mm,yes
